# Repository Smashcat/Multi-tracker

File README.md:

# Multi-tracker

### Tracking device dev board with Sigfox, Wifi and GPS functionality

This board is designed to allow testing and development of a tracking device using Sigfox, WiFi and GPS location tracking. It also breaks out all useful pins and indicators on both the WSS10R1AT Sigfox module, and the SIM28ML GPS module.

A P-channel mosfet supplies power to the GPS module, so that it can be enabled and disabled as needed to save power. The LEDs can also be enabled and disabled via a jumper, so that realistic power consumption tests can be performed if needed.

The ESP8266 has GPIO16 connected to reset, to allow the use of deep sleep, with timer interrupt wake.

The i2C pins from the ESP8266 are broken out onto the header, to allow connection of sensors, displays etc as needed. Additionally the ADC input from the ESP8266 has also been broken out - the input uses a voltage divider, so it can read voltages from 0 to around 3.3v.

Please note that this board is designed to run from 3.3V or lower, as it has no on-board voltage regulation. This is deliberate, as the board is designed for testing and development. If there is interest I will make another version more suited to outdoor use, with regulator, charging circuit etc to run from lithium Ion batteries or a USB charger.

Gerbers are included, ready to be submitted to JLCPCB or PCBWay (not tested with other services)

3D model render with CAD download can be found [here](https://a360.co/2Z3gr4b)

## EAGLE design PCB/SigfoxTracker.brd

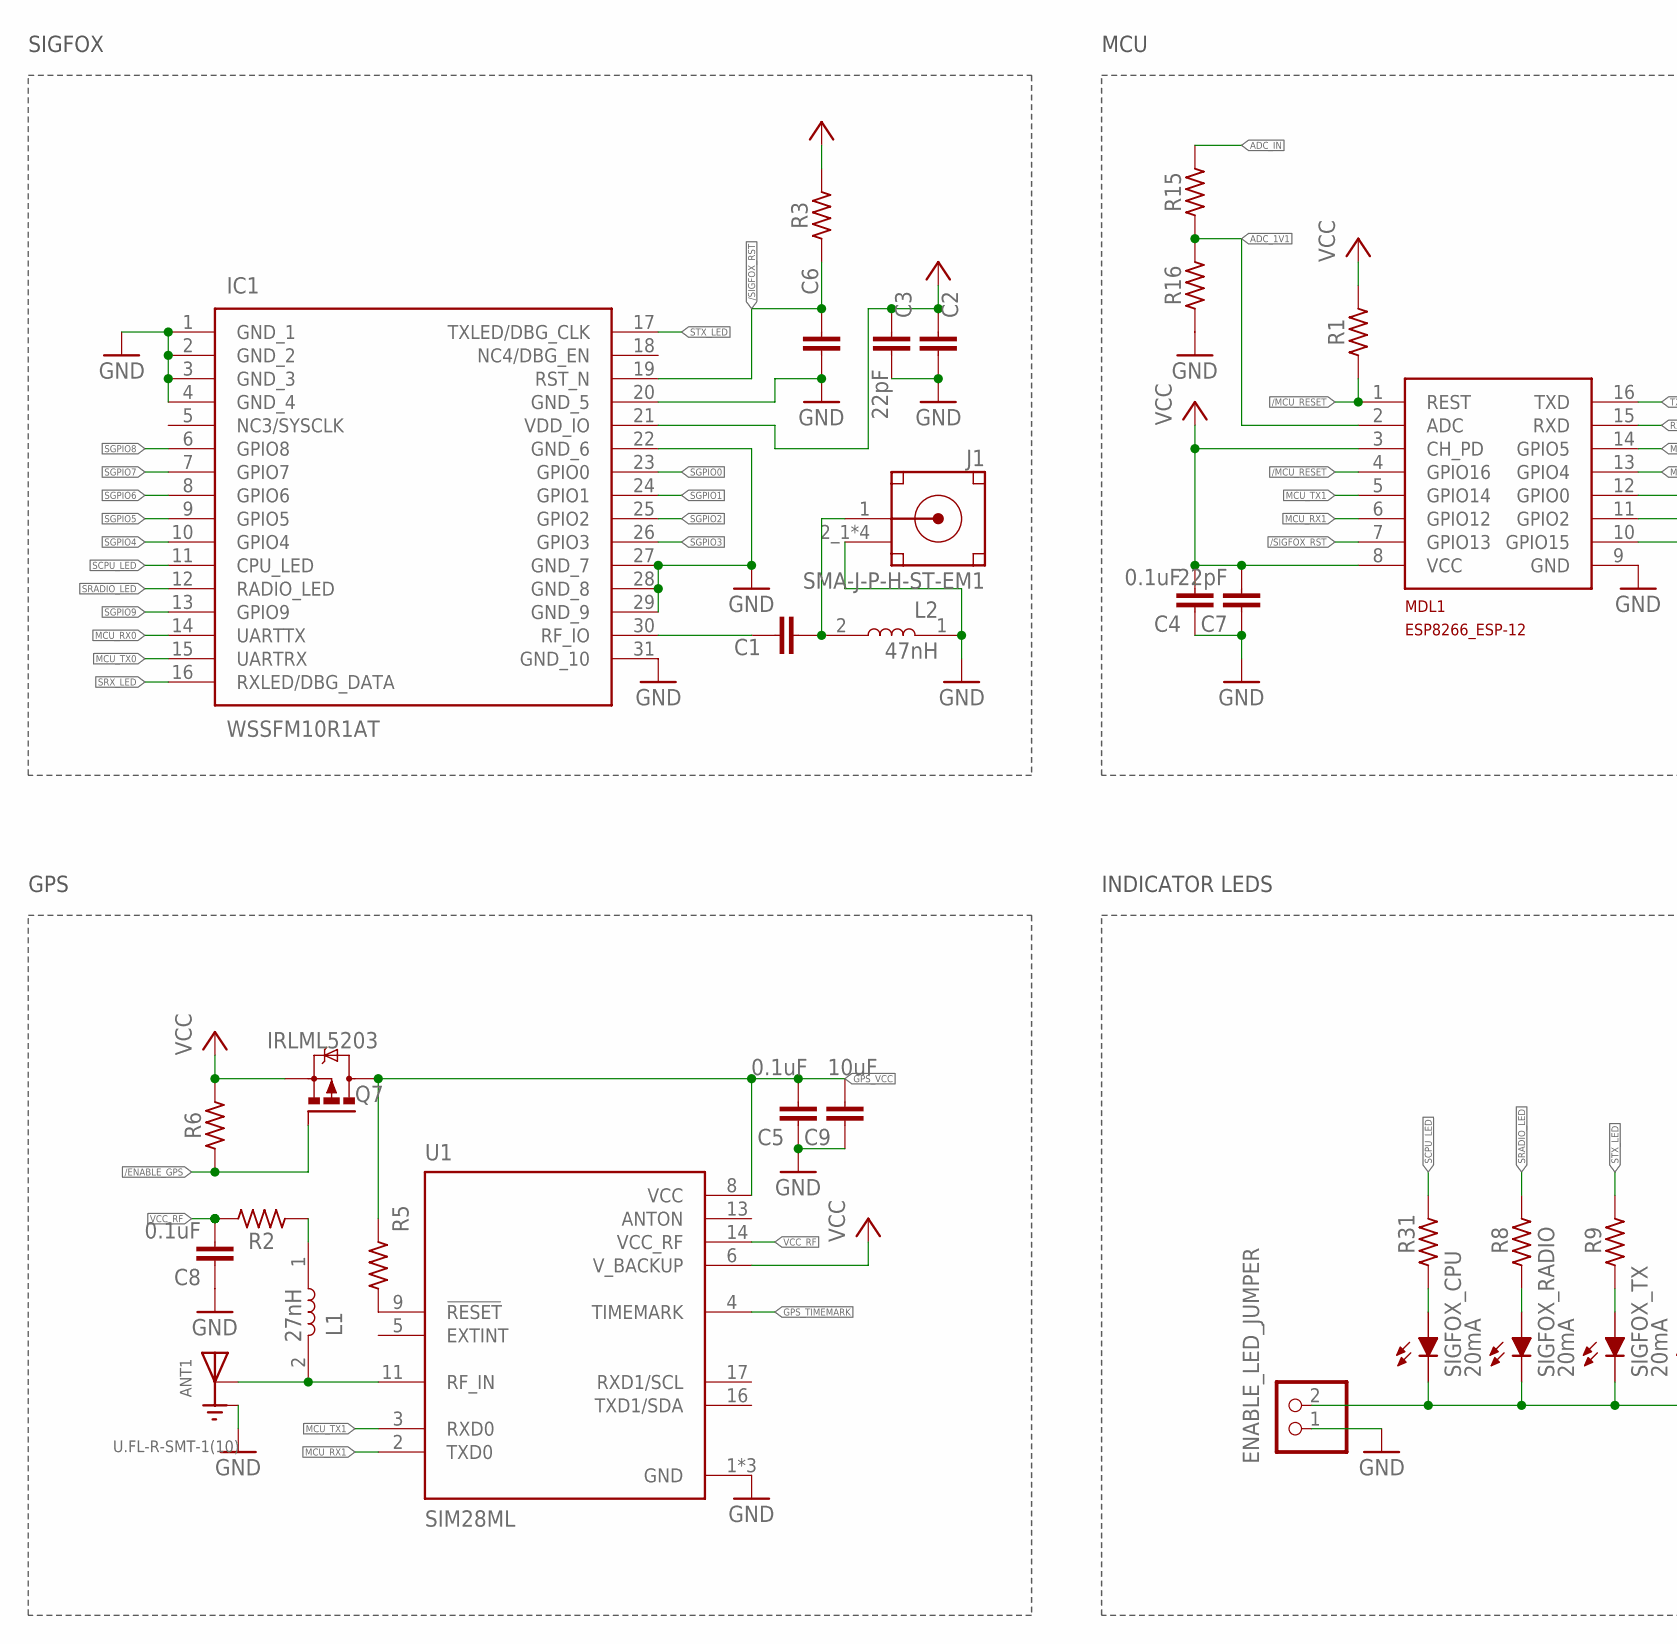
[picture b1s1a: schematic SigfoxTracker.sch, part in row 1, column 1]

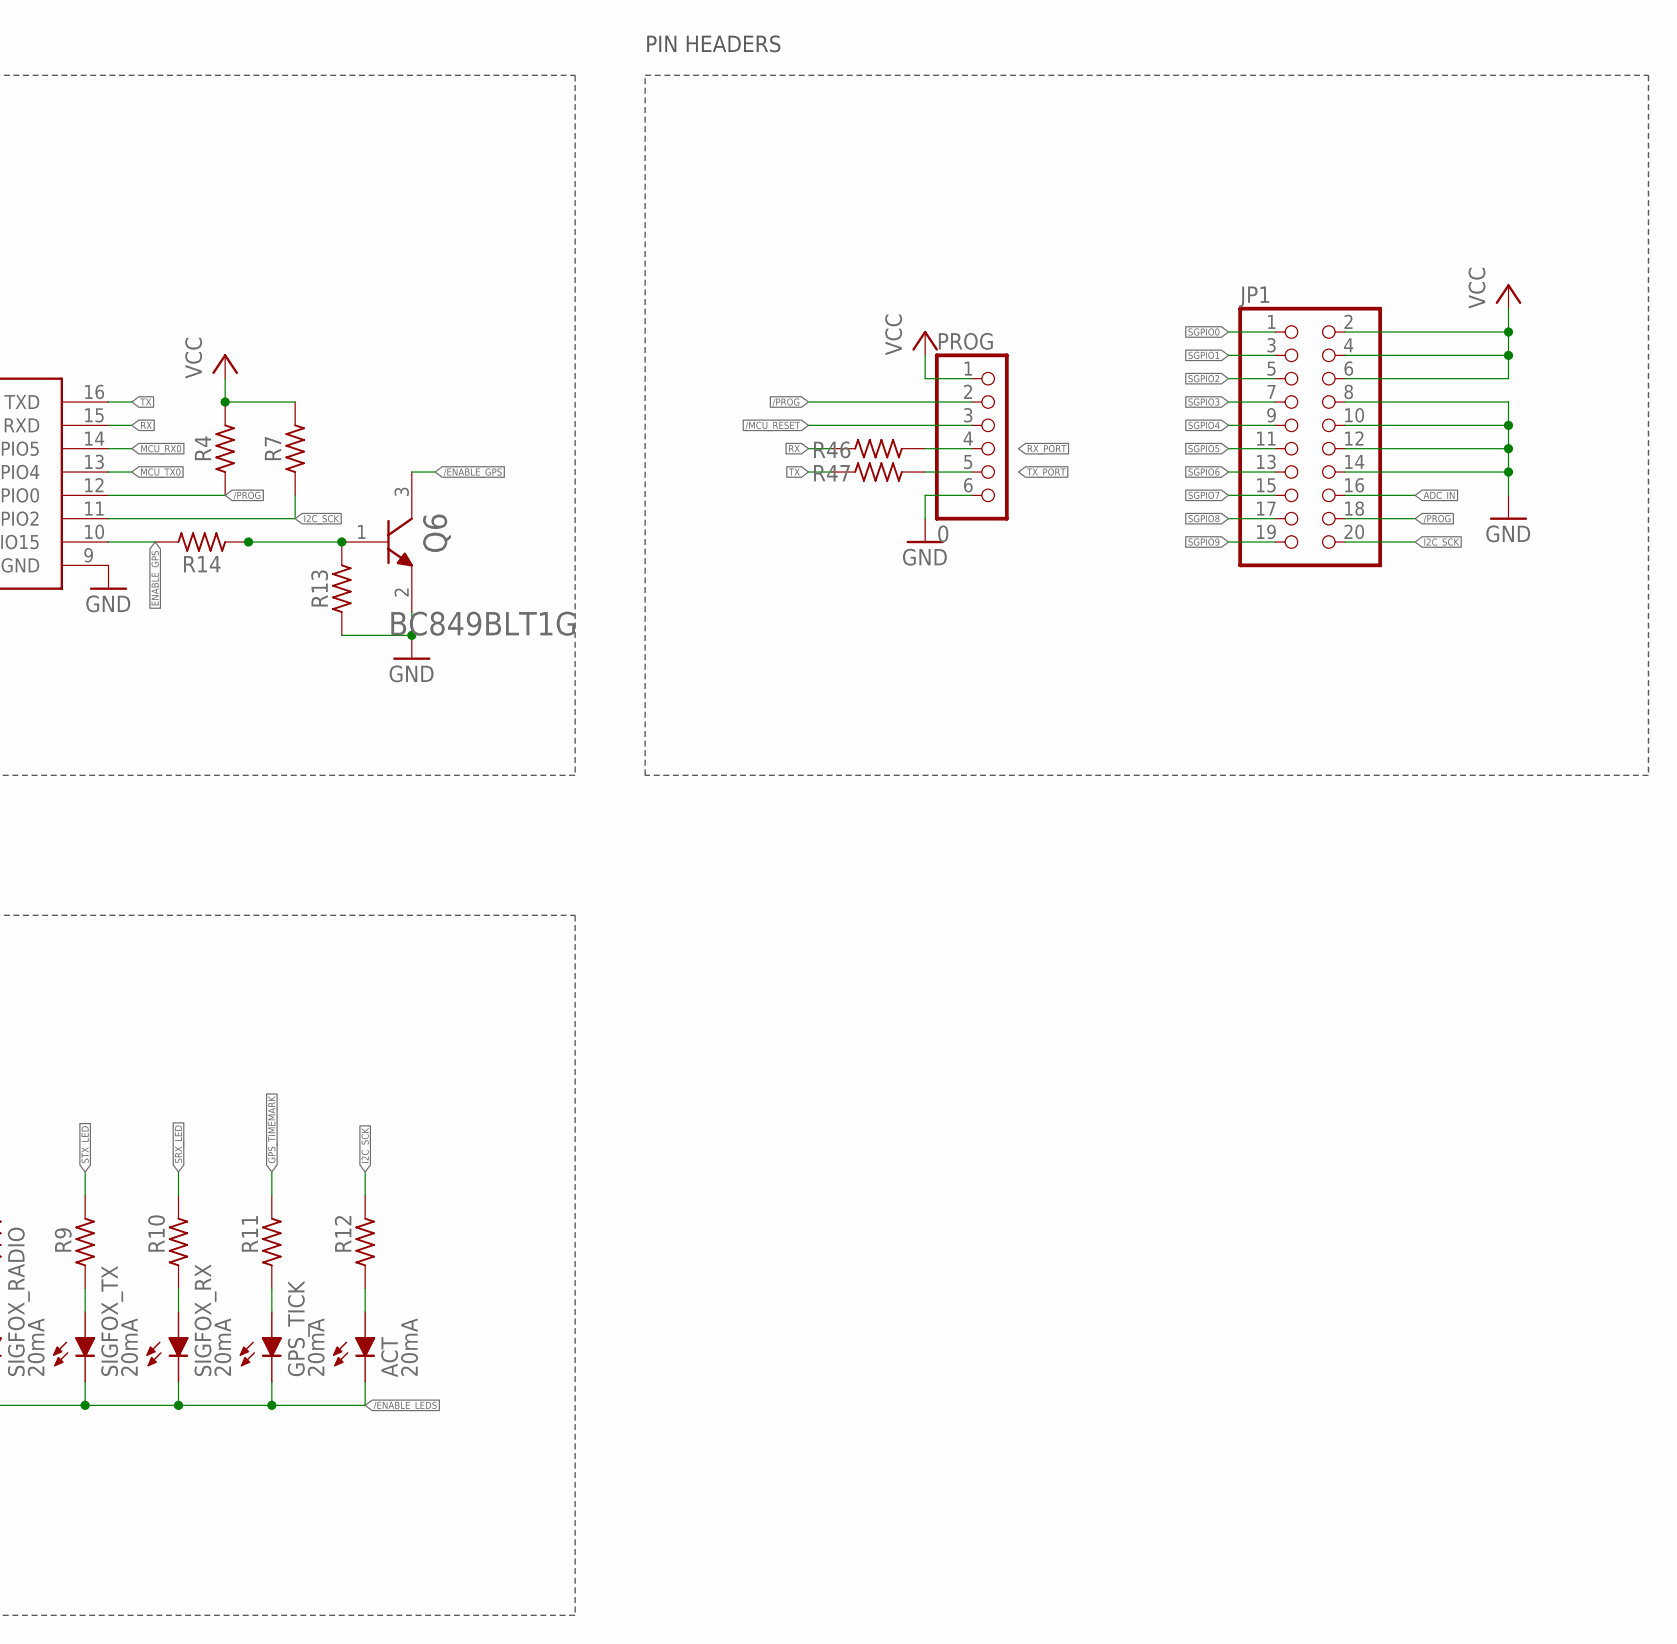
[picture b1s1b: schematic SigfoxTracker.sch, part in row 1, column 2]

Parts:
ACT: 20mA; LED_CHIP-LED0603MP
ANT1: U.FL-R-SMT-1(10); HRS_U.FL-R-SMT-1(10)
C1: 100pF; C0603
C2, C4, C5, C6, C8: 0.1uF; C0603
C3, C7: 22pF; C0603
C9: 10uF; C0603
ENABLE_LED_JUMPER: PINHD-1X2; 1X02
GPS_TICK: 20mA; LED_CHIP-LED0603MP
IC1: WSSFM10R1AT
J1: SMA-J-P-H-ST-EM1
JP1: PINHD-2X10; 2X10
L1: 27nH; INDC1005X45
L2: 47nH; INDC1005X45
MDL1: MCU; ESP8266-ESP12
PROG: 0; 1X06
Q6: ON_SEMICONDUCTOR_BC849BLT1GON_SEMICONDUCTOR_BC849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; ON_SEMICONDUCTOR_BC849BLT1G_0
Q7: IRLML5203; MICRO3
R1, R5, R13: 100k; 52101-101-REV-A_RC-MASTER-SMD_R0603MP
R2: 10R; RC-MASTER-SMD_R0603MP
R3, R6: 100K; RC-MASTER-SMD_R0603MP
R4, R7: 4K7; 52101-101-REV-A_RC-MASTER-SMD_R0603MP
R8, R9, R10, R11, R12, R14, R31: 1K; 52101-101-REV-A_RC-MASTER-SMD_R0603MP
R15: 10K; 52101-101-REV-A_RC-MASTER-SMD_R0603MP
R16: 3V3; 52101-101-REV-A_RC-MASTER-SMD_R0603MP
R46, R47: 20R; RC-MASTER-SMD_R0603MP
SIGFOX_CPU: 20mA; LED_CHIP-LED0603MP
SIGFOX_RADIO: 20mA; LED_CHIP-LED0603MP
SIGFOX_RX: 20mA; LED_CHIP-LED0603MP
SIGFOX_TX: 20mA; LED_CHIP-LED0603MP
U1: SIM28ML; XCVR_SIM28ML

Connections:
/ENABLE_GPS: Q6.3 (C), Q7.1 (G), R6.1
/ENABLE_LEDS: ACT.C, ENABLE_LED_JUMPER.2, GPS_TICK.C, SIGFOX_CPU.C, SIGFOX_RADIO.C, SIGFOX_RX.C, SIGFOX_TX.C
/MCU_RESET: MDL1.1 (REST), MDL1.4 (GPIO16), PROG.3, R1.1
/PROG: JP1.18, MDL1.12 (GPIO0), PROG.2, R4.1
/SIGFOX_RST: C6.1, IC1.19 (RST_N), MDL1.7 (GPIO13), R3.1
ADC_1V1: MDL1.2 (ADC), R15.1, R16.2
ADC_IN: JP1.16, R15.2
ANTON: U1.13 (ANTON)
ENABLE_GPS: MDL1.10 (GPIO15), R14.2
GND: ANT1.1 (GND), ANT1.3 (GND), C2.1, C3.1, C4.1, C5.1, C6.2, C7.1, C8.1, C9.1, ENABLE_LED_JUMPER.1, IC1.1 (GND_1), IC1.2 (GND_2), IC1.3 (GND_3), IC1.4 (GND_4), IC1.20 (GND_5), IC1.22 (GND_6), IC1.27 (GND_7), IC1.28 (GND_8), IC1.29 (GND_9), IC1.31 (GND_10), J1.2_1 (GND), J1.2_2 (GND), J1.3_1 (GND), J1.3_2 (GND), JP1.8, JP1.10, JP1.12, JP1.14, L2.1, MDL1.9 (GND), PROG.6, Q6.2 (E), R13.1, R16.1, U1.1 (GND), U1.10 (GND), U1.12 (GND)
GPS_TIMEMARK: R11.1, U1.4 (TIMEMARK)
GPS_VCC: C5.2, C9.2, Q7.3 (D), R5.2, U1.8 (VCC)
I2C_SCK: JP1.20, MDL1.11 (GPIO2), R7.1, R12.1
MCU_RX0: IC1.14 (UARTTX), MDL1.14 (GPIO5)
MCU_RX1: MDL1.6 (GPIO12), U1.2 (TXD0)
MCU_TX0: IC1.15 (UARTRX), MDL1.13 (GPIO4)
MCU_TX1: MDL1.5 (GPIO14), U1.3 (RXD0)
unnamed: R5.1, U1.9 (!RESET)
unnamed: C1.2, J1.1 (SIGNAL), L2.2
unnamed: L1.1, R2.1
unnamed: R8.2, SIGFOX_RADIO.A
unnamed: R9.2, SIGFOX_TX.A
unnamed: R10.2, SIGFOX_RX.A
unnamed: GPS_TICK.A, R11.2
unnamed: ACT.A, R12.2
unnamed: R31.2, SIGFOX_CPU.A
unnamed: Q6.1 (B), R13.2, R14.1
RF_IN: ANT1.2 (SIG), L1.2, U1.11 (RF_IN)
RX: MDL1.15 (RXD), R46.1
RX_PORT: PROG.4, R46.2
SCPU_LED: IC1.11 (CPU_LED), R31.1
SGPIO0: IC1.23 (GPIO0), JP1.1
SGPIO1: IC1.24 (GPIO1), JP1.3
SGPIO2: IC1.25 (GPIO2), JP1.5
SGPIO3: IC1.26 (GPIO3), JP1.7
SGPIO4: IC1.10 (GPIO4), JP1.9
SGPIO5: IC1.9 (GPIO5), JP1.11
SGPIO6: IC1.8 (GPIO6), JP1.13
SGPIO7: IC1.7 (GPIO7), JP1.15
SGPIO8: IC1.6 (GPIO8), JP1.17
SGPIO9: IC1.13 (GPIO9), JP1.19
SIGFOX_RF_IO: C1.1, IC1.30 (RF_IO)
SRADIO_LED: IC1.12 (RADIO_LED), R8.1
SRX_LED: IC1.16 (RXLED/DBG_DATA), R10.1
STX_LED: IC1.17 (TXLED/DBG_CLK), R9.1
TX: MDL1.16 (TXD), R47.1
TX_PORT: PROG.5, R47.2
VCC: C2.2, C3.2, C4.2, C7.2, IC1.21 (VDD_IO), JP1.2, JP1.4, JP1.6, MDL1.3 (CH_PD), MDL1.8 (VCC), PROG.1, Q7.2 (S), R1.2, R3.2, R4.2, R6.2, R7.2, U1.6 (V_BACKUP)
VCC_RF: C8.2, R2.2, U1.14 (VCC_RF)

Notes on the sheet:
SIGFOX
GPS
INDICATOR LEDS
MCU
PIN HEADERS

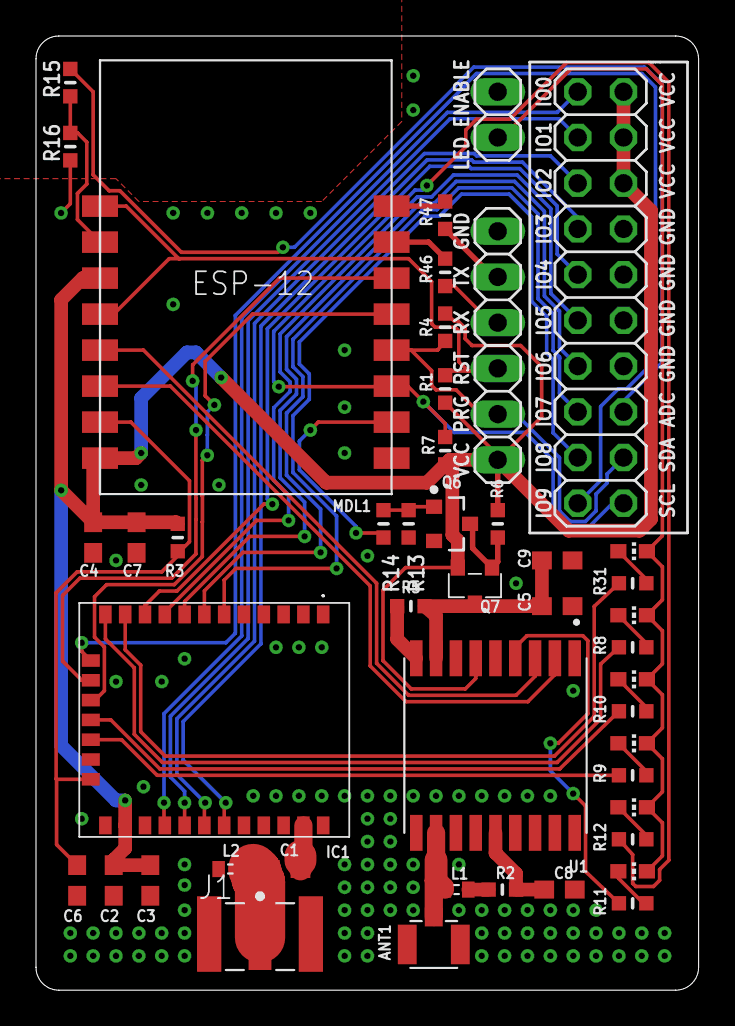
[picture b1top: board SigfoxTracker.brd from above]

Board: 2 copper layers, 36.8 x 53.0 mm, 46 parts (0 on the bottom side), 48 nets.

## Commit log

2020-08-25 Adding files
2020-08-25 Added some labels for LEDs to back of board
2020-08-29 More stitching, cleaned up schematic
2020-08-29 New Gerbers and updated README
2020-08-29 Better render image
2020-08-29 Removed old render
2020-08-29 Create LICENSE
2020-09-05 New revision, broken out i2C, ADC input, changed silkscreen
2020-09-05 Updated README with details to reflect the updated board design
2020-09-05 Added tech docs for major components
